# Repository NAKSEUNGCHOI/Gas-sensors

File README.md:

# Project Gas(Air quality) sensors

* University of Washington Summer 2022 
* Prof. Vikram Iyer.
* Nakseung Choi | graduate research assistant @ SSOL UW 

## Description

* Prof. Vikram Iyer and I are currently building low power low cost gas sensors (CO2, CO, and black carbon) to help two groups of scientists collect data for their research studies. One group wants to get data in the greater Seattle area to study on where these gasses are coming from. Ultimately, they would like to expand the number of the gas sensors in different locations such that they can compare with other locations for further studies.
The other group would like to place these gas sensors in the middle of moutains in the eastern Washington to study how these gases(CO2 and CO) affect wild animals when there is an unexpected wildfire going. 

* We are currently testing several CO2 sensors to compare their functionality with a commercial device. In the mean time, we just got done with our own PCB design for SPEC CO sensor as well as hardware/software integration. Depending on how precise data the scientists need, we are going to make it acordingly. nRF52480 Arm Cortex-m4 is probably going to be used for the MCU. Using Lora radio communication, a long distance communication interface will also be implemented to update data to the web server such that the scientists can check the data in real time.  

## Authors

- Nakseung Choi
- Please check out my Linkedin: https://www.linkedin.com/in/nakseung-choi-090a1b69/

## Release Notes

* <pre> New Tube arrived. About to go install the MA350 on the rooftop                       11-22-2022</pre>
* <pre> 300ml/min 60 ml/min for 5 wavelengths tests are done. missing 60 ml/min with UV+IR    9-12-2022</pre>
* <pre> Created another python code to draw different plots for CO2 sensors                   9-12-2022</pre>
* <pre> Wrote a python code to plot CO2 sensors - avg of two aranets for 4 sensors            9-08-2022</pre>
* <pre> wrote a python program using mathplot to graph the CO2 data  (Still testing MA350)    9-07-2022</pre>
* <pre> Testing the MA350                                                                     8-29-2022</pre>
* <pre> arduino / python serial communication script complete. Sending data to adafruitIO     8-26-2022</pre>
* <pre> presentation done. more CO testing / preparing to set up MA350.                       8-24-2022</pre>                                                
* <pre> got the CO sensor working with noise. more testing...........                         8-23-2022</pre>
* <pre> created a new PCB board and testing..                                                 8-22-2022</pre>
* <pre> presentation preparation2                                                             8-20-2022</pre>
* <pre> presentation preparation                                                              8-20-2022</pre>
* <pre> Software done. software/hardware integration started                                  8-18-2022</pre>
* <pre> Testing CO sensor 2                                                                   8-17-2022</pre>
* <pre> Testing CO sensor                                                                     8-16-2022</pre>
* <pre> setting up Black Carbon sensor & CO sensor                                            8-15-2022</pre>
* <pre> testing two SCD41s, two aranets, two PASCO2s all together.                            8-15-2022</pre>
* <pre>Debugging Complete. Ready to go for a testing.                                         8-14-2022</pre>
* <pre>Debugging...                                                                           8-12-2022</pre>
* <pre>PASCO2s are going to be tested with scd41 and aranet4 together for the functionality   8-11-2022</pre>
* <pre>Xensiv PAS CO2 coding in python complete.                                              8-11-2022</pre>
* <pre>Xensiv PAS CO2 working. Testing started.                                               8-10-2022</pre>
* <pre>Debugging Xensiv PAS CO2                                                               8-09-2022</pre>
* <pre>Testing Xensiv PAS CO2 manufactured by Infineon.                                       8-08-2022</pre>
* <pre>All parts are done soldering onto the board. Going to test the PCB.                    8-07-2022</pre>
* <pre>CO sensor PCB design complete. About to sorder the CO sensor circuit.                  8-03-2022</pre> 
* <pre>Designing a new circuit for CO sensor due to the chip shortage (LMP9100 out of stock)  8-02-2022</pre>
* <pre>Installed CO2 sensor's in an office with two people.                                   7-28-2022</pre>
* <pre>CO Sensor PCB Design V2 complete.                                                      7-28-2022</pre>
* <pre>CO Sensor PCB Design complete.                                                         7-27-2022</pre>
* <pre>Testing 24 hours success.                                                              7-26-2022</pre>
* <pre>Testing two SCD41s and two aranets4s on Raspberry pi 3.                                7-25-2022</pre>
* <pre>Working on PCB design for CO sensor                                                    7-24-2022</pre>
* <pre>Implemented two SCD41s and two aranet4s on Raspberry pi 3 for a testing.               7-21-2022</pre>
* <pre>Implemented SCD41 on nRF52480 express with Lora Radio (RFM9x)                          7-07-2022</pre>
* <pre>Implemented SCD41 (via I2C) and Aranet4 (via Bluetooth) on Raspberry pi 3 (B type)     7-01-2022</pre>
* <pre>Started                                                                                6/24/2022</pre>

## License

Copyright @ Nakseung Choi.

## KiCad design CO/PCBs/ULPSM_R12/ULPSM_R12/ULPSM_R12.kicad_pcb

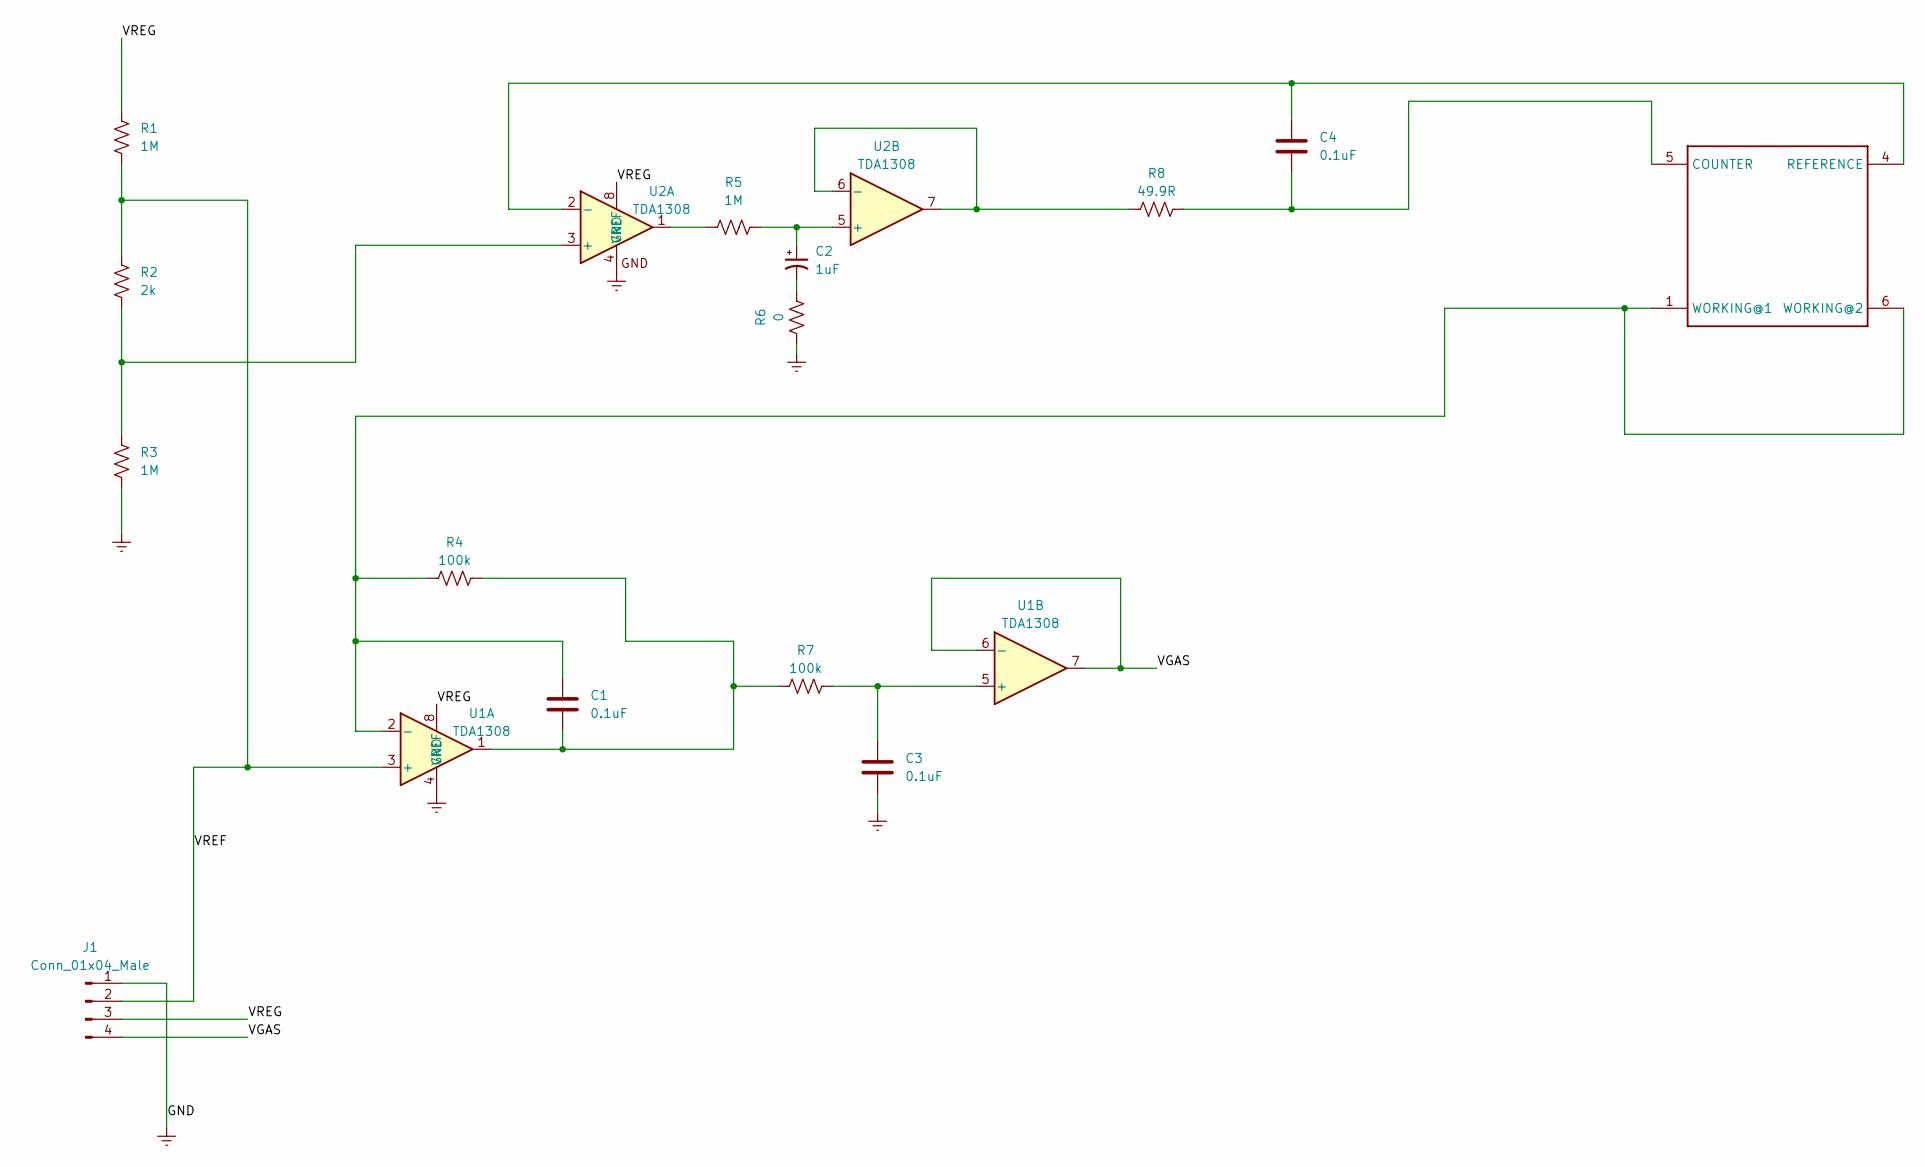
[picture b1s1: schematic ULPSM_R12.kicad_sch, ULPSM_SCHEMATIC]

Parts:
C1, C3, C4: 0.1uF; C_0805_2012Metric
C2: 1uF; F951E105MPAAQ2
J1: Conn_01x04_Male; PinSocket_1x04_P2.54mm_Vertical
R1, R3, R5: 1M; R_0805_2012Metric
R2: 2k; R_0805_2012Metric
R4, R7: 100k; R_0805_2012Metric
R6: 0; R_0805_2012Metric
R8: 49.9R; R_0805_2012Metric
SENS-CO1: SPECSENSOR; 3SP_CO_1000_P_Package_2
U1, U2: TDA1308; MCP6042T-I&slash_MS

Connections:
/VGAS: J1.4, U1.6 (-), U1.7
/VREF: J1.2, R1.2, R2.1, U1.3 (+)
/VREG: J1.3, R1.1, U1.8 (VREF), U2.8 (VREF)
Earth: C3.2, J1.1, R3.2, R6.1, U1.4 (GND), U2.4 (GND)
unnamed: C1.1, R4.1, SENS-CO1.1 (WORKING@1), SENS-CO1.6 (WORKING@2), U1.2 (-)
unnamed: C1.2, R4.2, R7.1, U1.1
unnamed: C2.1, R5.2, U2.5 (+)
unnamed: C2.2, R6.2
unnamed: C3.1, R7.2, U1.5 (+)
unnamed: C4.1, SENS-CO1.4 (REFERENCE), U2.2 (-)
unnamed: C4.2, R8.2, SENS-CO1.5 (COUNTER)
unnamed: R2.2, R3.1, U2.3 (+)
unnamed: R5.1, U2.1
unnamed: R8.1, U2.6 (-), U2.7

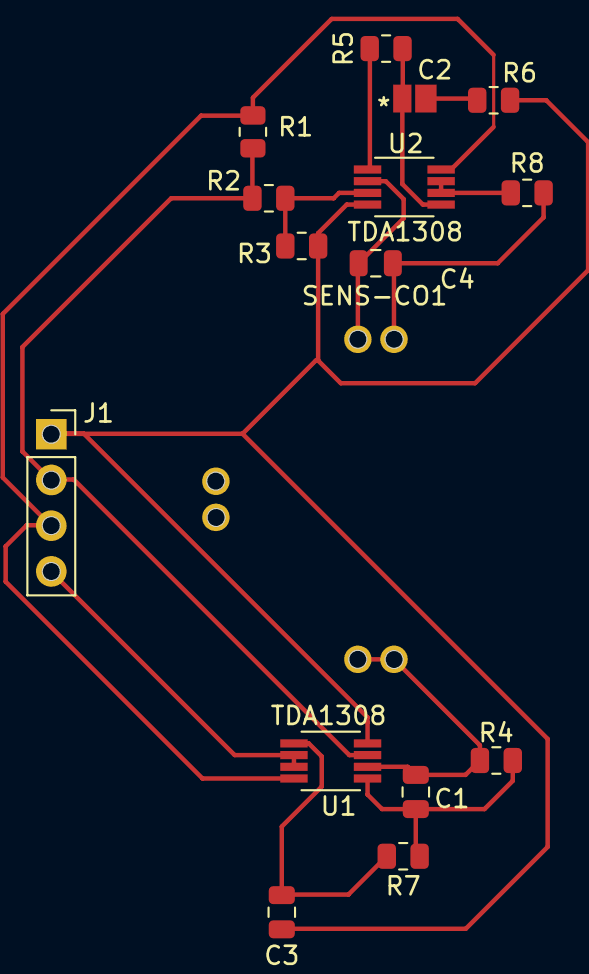
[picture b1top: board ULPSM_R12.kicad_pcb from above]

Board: 2 copper layers, 16 parts (0 on the bottom side), 14 nets.

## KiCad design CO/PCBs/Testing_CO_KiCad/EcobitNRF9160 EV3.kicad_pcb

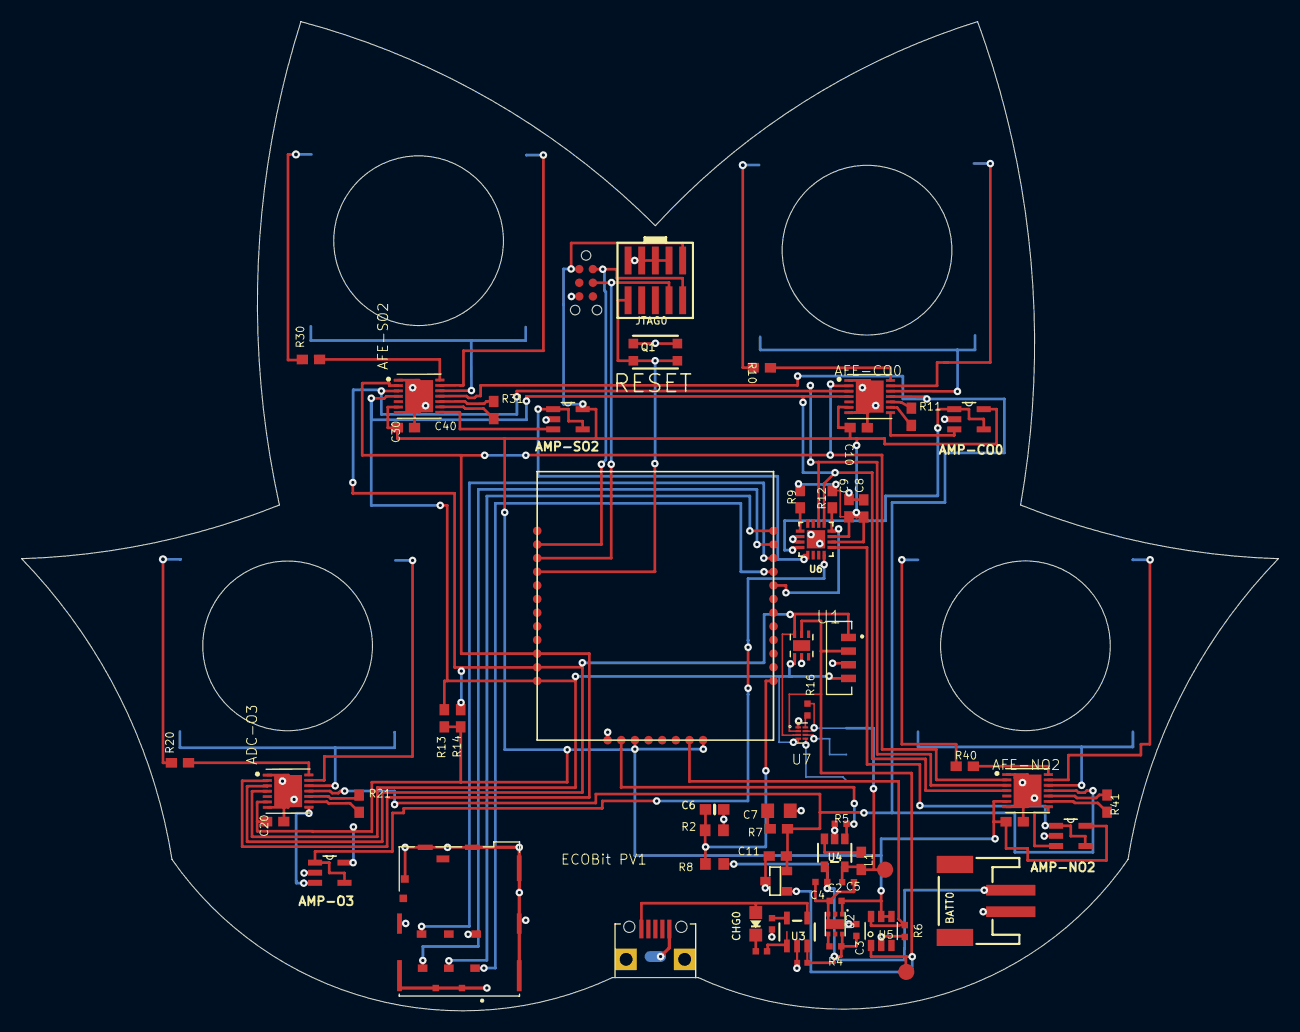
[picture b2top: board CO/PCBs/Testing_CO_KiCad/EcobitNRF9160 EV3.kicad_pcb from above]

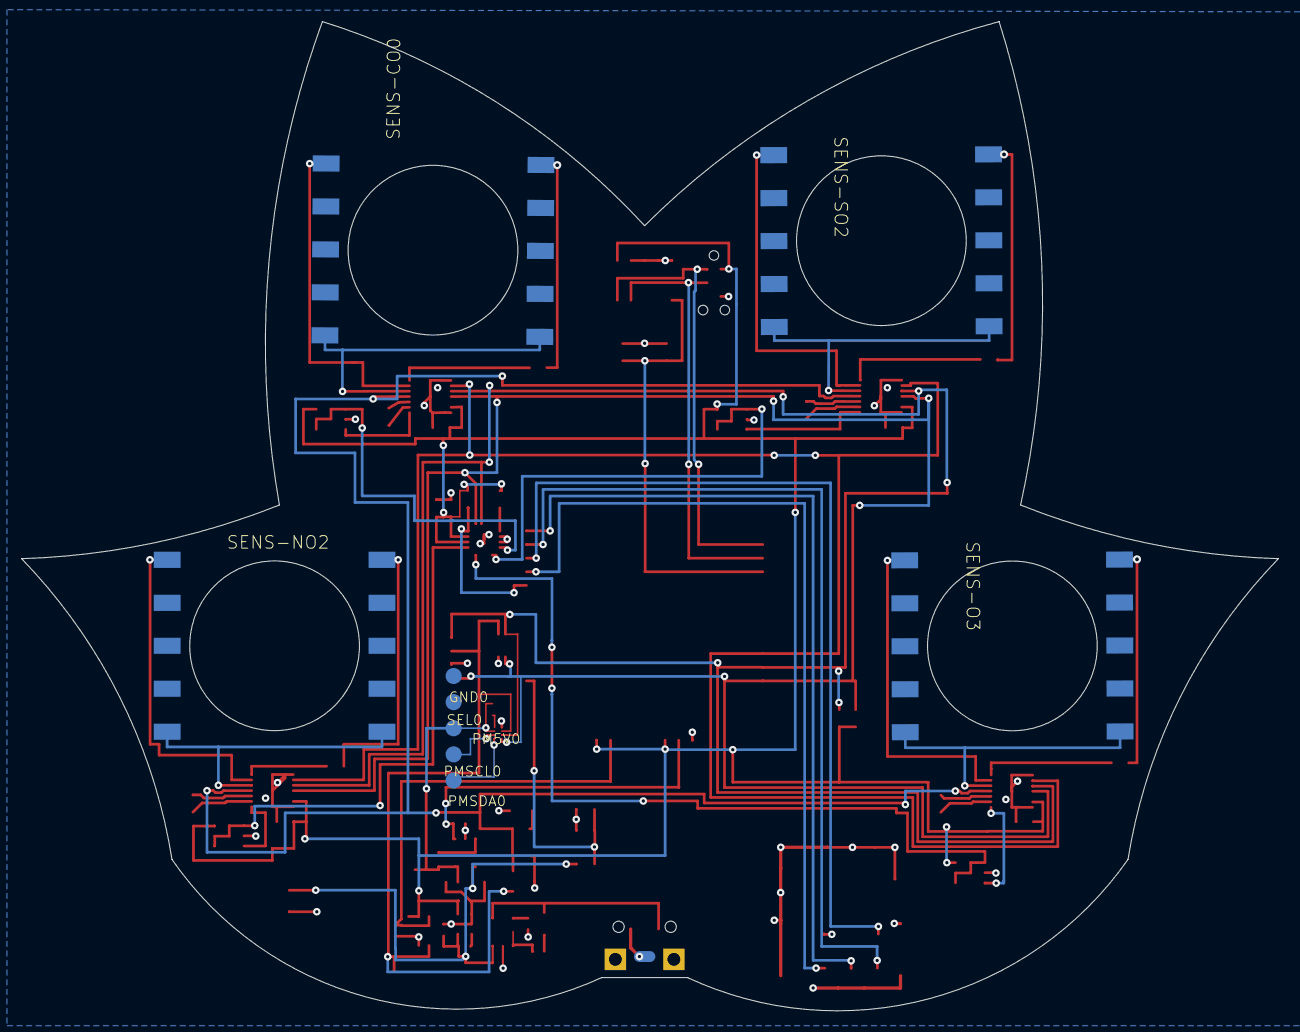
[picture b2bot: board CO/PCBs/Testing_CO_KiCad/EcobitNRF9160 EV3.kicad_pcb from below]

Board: 4 copper layers, 117.0 x 92.1 mm, 72 parts (9 on the bottom side), 63 nets.

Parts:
ADC-O3: LMP91000SD/NOPB; SON50P400X400X80-15N
AFE-CO0: LMP91000SD/NOPB; SON50P400X400X80-15N
AFE-NO2: LMP91000SD/NOPB; SON50P400X400X80-15N
AFE-SO2: LMP91000SD/NOPB; SON50P400X400X80-15N
AMP-CO0: MCP6041T-E/OT; SOT95P320X145-5N
AMP-NO2: MCP6041T-E/OT; SOT95P320X145-5N
AMP-O3: MCP6041T-E/OT; SOT95P320X145-5N
AMP-SO2: MCP6041T-E/OT; SOT95P320X145-5N
BATT0: 3-6VDC; JSTPH2
C1: 10uF; C-0402
C2, C3, C4, C5: 1uF; RESC0402_N
C6: 1nF; 0603-NO
C7: 10uF 10V 20% Tant; RESC0805_N
C8, C9, C10, C11, C20, C30, C40: 0.1uF; RESC0603_N
CHG0: CHIPLED_0805_NOOUTLINE
GND0: TPTP15R; TP15R
IC1: ISL60002DIH320Z-TK; SOT-23-3
J2: TC2030-MCP-NL
JP1: USB-RECEPTABLE; FCI-10103594-0001LF
JTAG0: 2X05_1.27MM_SMT
L1: 22nH; RESC0603_N
P1: SF72S006VBAR2500; JAE_SF72S006VBAR2500
PM5V0: TPTP15R; TP15R
PMSCL0: TPTP15R; TP15R
PMSDA0: TPTP15R; TP15R
Q1: Btn; BTN_KMR2_4.6X2.8
R1: 10k; R0402
R2: 2M; R0603
R3: 1k; R0402
R4, R5, R6: 10K; RESC0402_N
R7: 1k; RESC0603_N
R8: 806k; R0603
R9, R12: 10k; RESC0603_N
R10, R20, R30, R40: 49.9k; RESC0603_N
R11, R21, R31, R41: 499k; RESC0603_N
R13, R14: 4.7k; RESC0603_N
R16: 200K; RESC0402_N
SEL0: TPTP15R; TP15R
SENS-CO0: SPECSENSOR
SENS-NO2: SPECSENSOR
SENS-O3: SPECSENSOR
SENS-SO2: SPECSENSOR
U1: VEML7700-TR; XDCR_VEML7700-TR
U2: NCP718; NCP718-WDFN6
U3: MCP73831T-2ACI/OT; SOT23-5
U4: AP3418; SOT25
U5: TPS22860DBVR; R-PDSO-G6
U6: ADS122C04; QFN50P300X300X80-16N
U7: PCA9306; PSON35P135X100X50-8N
U$14: HDC1080; TI-S-PWSON-N6
U$35: NRF9160MODULE; NRF9160CASTALLATEDMODULE
UNK5VBUS0, UNK5VBUS1: TPTP15R; TP15R

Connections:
3V3ACC: IC1.1, U1.2, U5.1, U7.2, U$14.5, UNK5VBUS1.TP
3V3EN: R6.2, U5.6, U$35.7
5VBOOSTEN: R5.2, U4.1, U$35.2
5VBUS: C5.2, L1.2, PM5V0.TP, R16.2, U4.5, U7.7, UNK5VBUS0.TP
CO-AMPVOUT: AMP-CO0.1, AMP-CO0.4, U6.4
COVOUT: AFE-CO0.8, AMP-CO0.3
GND: ADC-O3.1, ADC-O3.7, ADC-O3.15, AFE-CO0.1, AFE-CO0.7, AFE-CO0.15, AFE-NO2.1, AFE-NO2.7, AFE-NO2.15, AFE-SO2.1, AFE-SO2.7, AFE-SO2.15, AMP-CO0.2, AMP-NO2.2, AMP-O3.2, AMP-SO2.2, BATT0.1, C1.2, C2.2, C3.2, C4.1, C5.1, C6.1, C7.2, C8.1, C9.1, C10.2, C11.2, C20.2, C30.2, C40.2, GND0.TP, IC1.3, J2.5, JP1.5, JTAG0.3, JTAG0.5, JTAG0.7, JTAG0.9, P1.C5, P1.G1, P1.G2, P1.G3, P1.G4, P1.G5, P1.G6, P1.G7, P1.G8, P1.G9, P1.G10, Q1.B, Q1.B', R1.1, R2.1, R5.1, R6.1, SEL0.TP, U1.3, U2.3, U2.7, U3.2, U4.2, U5.2, U6.2, U6.3, U6.17, U7.1, U$14.2, U$35.1
unnamed: R16.1, U7.8
unnamed: L1.1, U4.3
unnamed: R3.1, U3.1
unnamed: CHG0.C, R3.2
unnamed: AFE-CO0.9, R11.2
unnamed: AFE-CO0.10, R11.1
unnamed: R1.2, U3.5
unnamed: AFE-CO0.14, R10.2
unnamed: C7.1, R7.1
unnamed: ADC-O3.9, R21.2
unnamed: ADC-O3.10, R21.1
unnamed: ADC-O3.14, R20.2
unnamed: AFE-SO2.9, R31.2
unnamed: AFE-SO2.10, R31.1
unnamed: AFE-SO2.14, R30.2
unnamed: AFE-NO2.9, R41.2
unnamed: AFE-NO2.10, R41.1
unnamed: AFE-NO2.14, R40.2
NO2-AMPVOUT: AMP-NO2.1, AMP-NO2.4, U6.9
NO2VOUT: AFE-NO2.8, AMP-NO2.3
O3-AMPVOUT: AMP-O3.1, AMP-O3.4, U6.8
O3VOUT: ADC-O3.8, AMP-O3.3
R-EN: R4.1, U2.4
RESET: JTAG0.10, Q1.A, Q1.A', U$35.29
SCL: ADC-O3.3, AFE-CO0.3, AFE-NO2.3, AFE-SO2.3, R14.1, U1.1, U6.14, U7.3, U$14.6, U$35.22
SCL5V: PMSCL0.TP, U7.6
SDA: ADC-O3.4, AFE-CO0.4, AFE-NO2.4, AFE-SO2.4, R13.1, U1.4, U6.13, U7.4, U$14.1, U$35.21
SDA5V: PMSDA0.TP, U7.5
SIM1V8: P1.C1, U$35.17
SIMCLK: P1.C3, U$35.19
SIMIO: P1.C7, U$35.18
SIMRESET: P1.C2, U$35.20
SO2-AMPVOUT: AMP-SO2.1, AMP-SO2.4, U6.5
SO2VOUT: AFE-SO2.8, AMP-SO2.3
SPEC-CO-COUNTER: R10.1, SENS-CO0.6
SPEC-CO-REF: AFE-CO0.13, SENS-CO0.5
SPEC-CO-WKG: AFE-CO0.12, SENS-CO0.1, SENS-CO0.10
SPEC-NO2-COUNTER: R40.1, SENS-NO2.6
SPEC-NO2-REF: AFE-NO2.13, SENS-NO2.5
SPEC-NO2-WKG: AFE-NO2.12, SENS-NO2.1, SENS-NO2.10
SPEC-O3-COUNTER: R20.1, SENS-O3.6
SPEC-O3-REF: ADC-O3.13, SENS-O3.5
SPEC-O3-WKG: ADC-O3.12, SENS-O3.1, SENS-O3.10
SPEC-SO2-COUNTER: R30.1, SENS-SO2.6
SPEC-SO2-REF: AFE-SO2.13, SENS-SO2.5
SPEC-SO2-WKG: AFE-SO2.12, SENS-SO2.1, SENS-SO2.10
SWCLK: J2.4, JTAG0.4, U$35.30
SWDIO: J2.2, JTAG0.2, U$35.31
VBAT: BATT0.2, C1.1, C3.1, C4.2, R4.2, R8.2, U2.6, U3.3, U4.4
VBUS: CHG0.A, JP1.1, U3.4
VDD: ADC-O3.6, AFE-CO0.6, AFE-NO2.6, AFE-SO2.6, AMP-CO0.5, AMP-NO2.5, AMP-O3.5, AMP-SO2.5, C2.1, C8.2, C9.2, C10.1, C20.1, C30.1, C40.1, J2.1, JTAG0.1, R9.2, R12.2, R13.2, R14.2, U2.1, U5.4, U5.5, U6.10, U6.11, U$35.3, U$35.8
VDIV: C6.2, R2.2, R8.1, U$35.9
VREFADC: ADC-O3.11, AFE-CO0.11, AFE-NO2.11, AFE-SO2.11, C11.1, IC1.2, R7.2
~DRDY: R12.1, U6.12, U$35.16
~GASSENS-EN: ADC-O3.2, AFE-CO0.2, AFE-NO2.2, AFE-SO2.2, U$35.23
~RESET: R9.1, U6.1

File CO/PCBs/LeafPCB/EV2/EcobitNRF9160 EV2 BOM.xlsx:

Column1 | Column2 | Column3 | Column4
Part | Value | Device | Package
ADC-CO | LMP91000SD/NOPB | LMP91000SD/NOPB | SON50P400X400X80-15N
ADC-NO2 | LMP91000SD/NOPB | LMP91000SD/NOPB | SON50P400X400X80-15N
ADC-O3 | LMP91000SD/NOPB | LMP91000SD/NOPB | SON50P400X400X80-15N
ADC-SO2 | LMP91000SD/NOPB | LMP91000SD/NOPB | SON50P400X400X80-15N
BATT | 3-6VDC | CON_JST_PH_2PIN | JSTPH2
C1 | 10uF | CAP0402 | C-0402
C2, C3, C4, C5, C6 | 1uF | CAPACITOR_0402_N | RESC0402_N
C7 | 10uF 10V 20% Tant | CAPACITOR_0805_N | RESC0805_N
C10, C11, C20, C30, C40 | 0.1uF | CAPACITOR_0603_N | RESC0603_N
CHG |  | LED0805_NOOUTLINE | CHIPLED_0805_NOOUTLINE
IC1 | ISL60002DIH320Z-TK | ISL60002DIH320Z-TK | SOT-23-3
JP1 | USB-RECEPTABLE | USB-RECEPTABLE | FCI-10103594-0001LF
L1 | 22nH | INDUCTOR_0603_N | RESC0603_N
P1 | SF72S006VBAR2500 | SF72S006VBAR2500 | JAE_SF72S006VBAR2500
Q1 | Btn | SWITCH_TACT_SMT4.6X2.8 | BTN_KMR2_4.6X2.8
R1, R4, R5, R6 | 10k | RESR0402 | R0402
R2 | 2M | R-US_R0603 | R0603
R3, R7 | 1k | RESR0402 | R0402
R11, R21, R31, R41 | 499k | RESISTOR_0603_N | RESC0603_N
R8 | 806k | R-US_R0603 | R0603
R10, R20, R30, R40 | 49.9k | RESISTOR_0603_N | RESC0603_N
IC2 | HDC1080 | HDC1080 | TI-S-PWSON-N6
U1 | VEML7700-TR | VEML7700-TR | XDCR_VEML7700-TR
U2 | NCP718 | NCP718 | NCP718-WDFN6
U3 | MCP73831T-2ACI/OT | MCP73831/2 | SOT23-5
U4 | AP3418 | AP3418 | SOT25
U5 | TPS22860DBVR | TPS22860DBVR | R-PDSO-G6
U6 | MCP6041T-I/OT

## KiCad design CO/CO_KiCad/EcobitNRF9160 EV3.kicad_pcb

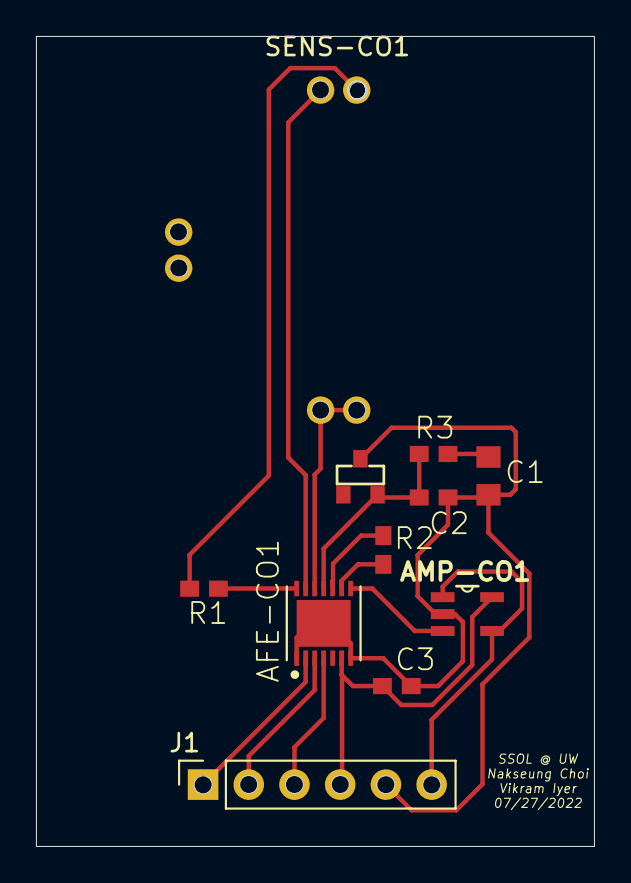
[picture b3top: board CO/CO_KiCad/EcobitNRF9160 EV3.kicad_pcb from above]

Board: 4 copper layers, 31.0 x 45.0 mm, 11 parts (0 on the bottom side), 15 nets.

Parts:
AFE-CO1: LMP91000SD/NOPB; SON50P400X400X80-15N
AMP-CO1: MCP6041T-E/OT; SOT95P320X145-5N
C1: 10uF 10V 20% Tant; RESC0805_N
C2, C3: 0.1uF; RESC0603_N
IC1: ISL60002DIH320Z-TK; SOT-23-3
J1: Conn_01x06_Male; PinSocket_1x06_P2.54mm_Vertical
R1, R2: 499k; RESC0603_N
R3: 1k; RESC0603_N
SENS-CO1: SPECSENSOR; 3SP_CO_1000_P_Package_2

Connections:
/CO-AMPVOUT: AMP-CO1.1 (VOUT), AMP-CO1.4 (VIN-), J1.6
/SCL: AFE-CO1.3 (SCL), J1.2
/SDA: AFE-CO1.4 (SDA), J1.3
/VDD: AFE-CO1.6 (VDD), AMP-CO1.5 (VDD), C3.1, J1.4
/VREFADC: AFE-CO1.11 (VREF), C2.1, IC1.2 (VOUT), R3.2
/~GASSENS-EN: AFE-CO1.2 (~MENB), J1.1
GND: AFE-CO1.1 (DGND), AFE-CO1.7 (AGND), AFE-CO1.15 (DAP), AMP-CO1.2 (VSS), C1.2, C2.2, C3.2, IC1.3 (GND), J1.5
unnamed: AFE-CO1.8 (VOUT), AMP-CO1.3 (VIN+)
unnamed: AFE-CO1.9 (C2), R2.2
unnamed: AFE-CO1.10 (C1), R2.1
unnamed: AFE-CO1.12 (WE), SENS-CO1.1 (WORKING@1), SENS-CO1.6 (WORKING@2)
unnamed: AFE-CO1.13 (RE), SENS-CO1.4 (REFERENCE)
unnamed: AFE-CO1.14 (CE), R1.2
unnamed: C1.1, R3.1
unnamed: R1.1, SENS-CO1.5 (COUNTER)

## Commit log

2022-07-28 CO Sensor PCB Design
2022-08-03 New CO PCB Design
2022-08-03 new pcb design for CO
2022-08-03 NEW PCB DESIGN
2022-08-08 noted
2022-08-09 debugging
2022-09-02 pulling

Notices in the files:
parts and their libraries:
©2009 ROFA.cz - modified and updated by Robert Darlington ‹rdarlington@gmail.com›
Copyright 2021 Accelerated Designs. All rights reserved.
